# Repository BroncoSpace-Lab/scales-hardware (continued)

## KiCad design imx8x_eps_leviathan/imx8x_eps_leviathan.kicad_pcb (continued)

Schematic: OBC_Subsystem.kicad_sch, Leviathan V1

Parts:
C20: 220n; C0402; Voltage Rating +50v; LCSC C5159775
C21, C24, C28, C29, C30, C31: 100n; C0402; Voltage Rating +50v; LCSC C85858
C22: 22n; C0402; Voltage Rating +50v; LCSC C77023
C23: 0.47u; C0402; Voltage Rating +25V; LCSC C1623
C25: 10p; C0402; Voltage Rating +50v; LCSC C1545
C26, C27: 47u; CAP-SMD_L7.3-W4.3-FD; Voltage Rating +35v; LCSC C87110
L2: 6.1u; IND-SMD_FTKB1207-6R1NT; LCSC C3040409
R15: 1k; R0402; LCSC C54968
R16: 56.2k; R0402; LCSC C54968
R17: 10k; R0402; LCSC C25531
R18: 1k; R0402; LCSC C106235
R19: 15k; R0402; LCSC C114761
R21, R22, R23: 15k; R0402; LCSC C25756
R24: 14k; R_0603_1608Metric; LCSC C2930066
R25: 17k; R_0603_1608Metric; LCSC C137788
R26: 47k; R0402; LCSC C93943
R27: 2k; R0402; LCSC C60488
R28: 110k; R0402; LCSC C138065
R29, R30, R33, R34, R35, R36: 4.7k; R_0603_1608Metric; LCSC C99782
R31: 240k; R0402; LCSC C138029
R32: 100k; R0402; LCSC C60491
TP14, TP18, TP19, TP20, TP21, TP22: TestPoint; TestPoint_Pad_D1.0mm
U8: TPS1HB08BQPWPRQ1; HTSSOP-16_L5.0-W4.4-P0.65-LS6.4-TL-EP2.9; LCSC Part C3230075
U9: LTC6902; MSOP-10_L3.0-W3.0-P0.50-LS5.0-BL; LCSC C581012
U10: LT8612EUDE#PBF; QFN-28_L6.0-W3.0-P0.50-BL-EP; LCSC Part C580312
U11: TCA4307DGKR; VSSOP-8_L3.0-W3.0-P0.65-LS4.9-BL; LCSC Part C880333
U12: INA260AIPWR; TSSOP-16_L5.0-W4.4-P0.65-LS6.4-BL-1; LCSC Part C2155885

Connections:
+3.3V_OBC: C21.1, C30.1, C31.1, R24.1, R25.1, TP22.1, U9.1 (V+), U12.5 (A0), U12.10 (VS), U12.14 (IN-); also elsewhere on the board
+3.3V_OBC_Perif: C28.1, R29.1, R30.1, R33.1, R34.1, R35.1, R36.1, U11.8 (VCC); also elsewhere on the board
+V_Batt: C20.1, R16.2, TP14.1, U8.17 (VBB); also elsewhere on the board
GND: C20.2, C21.2, C22.2, C23.2, C26.2, C27.2, C28.2, C29.2, C30.2, C31.2, R17.1, R18.1, R19.1, R21.2, R22.2, R23.2, R27.2, R28.2, R32.2, U8.1 (GND), U9.8 (GND), U10.8 (PGND), U10.11 (GND), U10.25 (NC), U11.4 (GND), U12.4 (A1), U12.6 (GND); also elsewhere on the board
unnamed: R23.1, U8.15 (NC)
unnamed: R21.1, U8.16 (DIA_EN)
unnamed: R15.1, R16.1, R17.2, TP18.1, U8.4 (EN)
unnamed: R19.2, U8.3 (LATCH)
unnamed: R22.1, U8.14 (SEL1)
unnamed: R18.2, U8.2 (SNS)
unnamed: R24.2, U9.9 (MOD)
unnamed: R25.2, U9.10 (SET)
unnamed: C25.1, C26.1, C27.1, L2.2, R31.1, TP21.1, U10.22 (BIAS), U12.1 (IN+), U12.12 (VBUS)
unnamed: C24.1, U10.20 (BST)
unnamed: R26.2, R27.1, U10.4 (EN/UV)
unnamed: C25.2, R31.2, R32.1, U10.24 (FB)
unnamed: C29.1, U10.21 (INTVCC)
unnamed: R28.1, U10.3 (RT)
unnamed: C24.2, L2.1, U10.15 (SW)
unnamed: C23.1, U10.2 (TR/SS)
unnamed: C22.1, R26.1, TP19.1, U8.6 (VOUT), U10.5 (VIN)
unnamed: R33.2, U11.1 (EN)
unnamed: R34.2, U11.5 (READY)
SCL: R30.2, U11.3 (SCLIN), U12.9 (SCL); also elsewhere on the board
SDA: R29.2, U11.6 (SDAIN), U12.8 (SDA); also elsewhere on the board
SYNC_PHASE1: TP20.1, U9.4 (OUT1), U10.1 (SYNC)
SYNC_PHASE2: U9.5 (OUT2); also elsewhere on the board
SYNC_PHASE3: U9.6 (OUT3); also elsewhere on the board
X_ADMA_I2C0_SCL: R35.2, U11.2 (SCLOUT); also elsewhere on the board
X_ADMA_I2C0_SDA: R36.2, U11.7 (SDAOUT); also elsewhere on the board
~WD_EN_OBC: R15.2; also elsewhere on the board

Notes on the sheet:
Clock
OBC Subsystem
I2C Buffer
All Power related caps must +50v 0603/0402. Logic side can be 25V~16V 0402. Aim for getting them all to be ceramics, this is for flight readiness.
Clock is brought up with LT8612 OBC output. Set to 400Khz, SSFM on. 3 Phase setting
R63 and R64 set UVLO @ 24v.
Note: Symbol was modified so that pins were consolidated. This is chip is version B, so pin 5 is ILIM
LT8612 Config SYNC (Tied to Clock Phase 2) RT (Set default frequency to 400khz EN/UV threshold (~24v = UV, due to Li-ion discharge PGND (Tie to GND) DONE SW (Tie to inductor and setup the boost capacitor) BST (add 0.1uF bypass cap) INTVCC (add 0.1uF bypass cap) BIAS (If Vout is greater than 3.3v ti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
Vbatt = [24.0, 28.8, 33.6] Due to Li-ion battery charged and discharged states
L is calculated to 6.09u. Avoid Rounding.
SNS -> 1k -> GND : Not Using Latch -> 15k -> GND : Auto-retry Enabled SEL1 & SEL2 -> 15k -> GND : Diagnostics Disabled ILIM -> FLOAT -> Default Current Limit Set 42A
R65 and R66 set 3.3V Vout.
Vout -> 22nF Cap (Pg. 38)
C23 Changing to 0.47 for ~200ms startup time.
R16/R17 voltage divider to ensure at both high and low Lipo levels. OBC is always on. EN Pin pulled low by WD_EN_OBC on WD timeout
A0->Vs A1->GND I2C Address 1000001

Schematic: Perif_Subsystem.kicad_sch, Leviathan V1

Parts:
C32: 220n; C0402; Voltage Rating +50v; LCSC C5159775
C33: 22n; C0402; Voltage Rating +50v; LCSC C77023
C34: 0.47u; C0402; Voltage Rating +25V; LCSC C1623
C35, C39, C40, C41: 100n; C0402; Voltage Rating +50v; LCSC C85858
C36: 10p; C0402; Voltage Rating +50v; LCSC C1545
C37, C38: 47u; CAP-SMD_L7.3-W4.3-FD; Voltage Rating +35v; LCSC C87110
CN1: DF11-16DP-2DSA(08); CONN-TH_DF11-16DP-2DSA-08; LCSC Part C530981
L3: 10u; IND-SMD_L8.0-W8.0; LCSC C2849554
R37: 1k; R0402; LCSC C114761
R38: 1k; R0402; LCSC C106235
R39, R41, R42, R43: 15k; R0402; LCSC C114761
R44: 47k; R0402; LCSC C93943
R45: 2k; R0402; LCSC C60488
R46: 110k; R0402; LCSC C138065
R47: 20.8k; R0402; LCSC C25766
R48: 5k; R0402; LCSC C477765
TP23, TP24, TP31, TP32, TP33, TP34: TestPoint; TestPoint_Pad_D1.0mm
U13: TPS1HB08BQPWPRQ1; HTSSOP-16_L5.0-W4.4-P0.65-LS6.4-TL-EP2.9; LCSC Part C3230075
U14: LT8612EUDE#PBF; QFN-28_L6.0-W3.0-P0.50-BL-EP; LCSC Part C580312
U15: INA260AIPWR; TSSOP-16_L5.0-W4.4-P0.65-LS6.4-BL-1; LCSC Part C2155885

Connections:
+3.3V_OBC: C40.1, U15.4 (A1), U15.5 (A0), U15.10 (VS); also elsewhere on the board
+5V_Perif: C41.1, CN1.1, CN1.2, CN1.3, CN1.4, CN1.5, CN1.6, CN1.7, CN1.8, TP34.1, U15.14 (IN-)
+V_Batt: C32.1, TP24.1, U13.17 (VBB); also elsewhere on the board
GND: C32.2, C33.2, C34.2, C37.2, C38.2, C39.2, C40.2, C41.2, CN1.9, CN1.10, CN1.12, CN1.14, CN1.16, R38.1, R39.1, R41.1, R42.1, R43.1, R45.2, R46.2, R48.2, U13.1 (GND), U14.8 (PGND), U14.11 (GND), U14.25 (NC), U15.6 (GND); also elsewhere on the board
unnamed: R43.2, U13.15 (NC)
unnamed: R41.2, U13.16 (DIA_EN)
unnamed: R37.1, TP23.1, U13.4 (EN)
unnamed: R39.2, U13.3 (LATCH)
unnamed: R42.2, U13.14 (SEL1)
unnamed: R38.2, U13.2 (SNS)
unnamed: C33.1, R44.1, TP31.1, U13.6 (VOUT), U14.5 (VIN)
unnamed: C36.1, C37.1, C38.1, L3.2, R47.1, TP33.1, U14.22 (BIAS), U15.1 (IN+), U15.12 (VBUS)
unnamed: C35.1, U14.20 (BST)
unnamed: R44.2, R45.1, U14.4 (EN/UV)
unnamed: C36.2, R47.2, R48.1, U14.24 (FB)
unnamed: C39.1, U14.21 (INTVCC)
unnamed: R46.1, U14.3 (RT)
unnamed: C35.2, L3.1, U14.15 (SW)
unnamed: C34.1, U14.2 (TR/SS)
SCL: U15.9 (SCL); also elsewhere on the board
SDA: U15.8 (SDA); also elsewhere on the board
SYNC_PHASE2: TP32.1, U14.1 (SYNC); also elsewhere on the board
X_LSIO_GPIO1_IO18: R37.2; also elsewhere on the board

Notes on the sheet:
Peripheral Subsystem
Gecko Connector
L is calculated to 9.065. Avoid rounding.
Switch can be reset from the OBC by toggling the EN line, so no watchdog needed.
LT8612 Config SYNC (Tied to Clock Phase 2) RT (Set default frequency to 400khz EN/UV threshold (~24v = UV, due to Li-ion discharge PGND (Tie to GND) DONE SW (Tie to inductor and setup the boost capacitor) BST (add 0.1uF bypass cap) INTVCC (add 0.1uF bypass cap) BIAS (If Vout is greater than 3.3v ti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
Vout -> 22nF Cap (Pg. 38)
A0->Vs A1->VS I2C Address 1000101
C12 Changing to 0.47 for ~200ms startup time. I think this was the main issue for the brown outs. We werent meeting the startup time.
R83 and R101 set UVLO @ 24v
R103 and R104 set 5V Vout
All Power related caps must +50v 0603/0402. Logic side can be 25V~16V 0402.

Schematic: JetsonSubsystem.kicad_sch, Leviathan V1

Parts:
C10: 220n; C0402; Voltage Rating +50v; LCSC C5159775
C11: 22n; C0402; Voltage Rating +50v; LCSC C77023
C12: 1u; C0402; Voltage Rating +10V; LCSC C14445
C13, C17, C18, C19: 100n; C0402; Voltage Rating +50v; LCSC C85858
C14: 10p; C0402; Voltage Rating +50v; LCSC C1545
C15, C16: 47u; CAP-SMD_L7.3-W4.3-FD; Voltage Rating +35v; LCSC C87110
J5: DF11-16DP-2DSA; CONN-TH_DF11-16DP-2DSA-08; LCSC Part C530981
L1: 35u; IND-SMD_L10.7-W10.0_ETQP5MXXXX; LCSC C2880058
R1, R2: 1k; R0402; LCSC C114761
R3, R5, R7, R8, R9: 15k; R0402; LCSC C114761
R4: 1k; R0402; LCSC C106235
R10: 47k; R0402; LCSC C93943
R11: 2k; R0402; LCSC C60488
R12: 110k; R0402; LCSC C138065
R13: 196k; R0402; LCSC C2077051
R14: 10k; R0402; LCSC C25531
TP1, TP2, TP10, TP11, TP12, TP13: TestPoint; TestPoint_Pad_D1.0mm
U5: TPS1HB08BQPWPRQ1; HTSSOP-16_L5.0-W4.4-P0.65-LS6.4-TL-EP2.9; LCSC Part C3230075
U6: LT8612EUDE#PBF; QFN-28_L6.0-W3.0-P0.50-BL-EP; LCSC Part C580312
U7: INA260AIPWR; TSSOP-16_L5.0-W4.4-P0.65-LS6.4-BL-1; LCSC Part C2155885

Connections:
+3.3V_OBC: C18.1, U7.10 (VS); also elsewhere on the board
+20V_Jetson: C19.1, J5.1, J5.2, J5.3, J5.4, J5.5, J5.6, J5.7, J5.8, TP13.1, U7.14 (IN-); also elsewhere on the board
+V_Batt: C10.1, TP2.1, U5.17 (VBB); also elsewhere on the board
GND: C10.2, C11.2, C12.2, C15.2, C16.2, C17.2, C18.2, C19.2, J5.9, J5.10, J5.11, J5.12, J5.13, J5.15, R3.2, R4.1, R5.2, R7.2, R8.2, R9.2, R11.2, R12.2, R14.2, U5.1 (GND), U6.8 (PGND), U6.11 (GND), U6.25 (NC), U7.4 (A1), U7.5 (A0), U7.6 (GND); also elsewhere on the board
unnamed: J5.14, J5.16
unnamed: R9.1, U5.15 (NC)
unnamed: R7.1, U5.16 (DIA_EN)
unnamed: R1.2, R2.1, R3.1, TP1.1, U5.4 (EN)
unnamed: R5.1, U5.3 (LATCH)
unnamed: R8.1, U5.14 (SEL1)
unnamed: R4.2, U5.2 (SNS)
unnamed: C11.1, R10.1, TP10.1, U5.6 (VOUT), U6.5 (VIN)
unnamed: C14.1, C15.1, C16.1, L1.2, R13.1, TP12.1, U6.22 (BIAS), U7.1 (IN+), U7.12 (VBUS)
unnamed: C13.1, U6.20 (BST)
unnamed: R10.2, R11.1, U6.4 (EN/UV)
unnamed: C14.2, R13.2, R14.1, U6.24 (FB)
unnamed: C17.1, U6.21 (INTVCC)
unnamed: R12.1, U6.3 (RT)
unnamed: C13.2, L1.1, U6.15 (SW)
unnamed: C12.1, U6.2 (TR/SS)
SCL: U7.9 (SCL); also elsewhere on the board
SDA: U7.8 (SDA); also elsewhere on the board
SYNC_PHASE3: TP11.1, U6.1 (SYNC); also elsewhere on the board
X_LSIO_GPIO1_IO19: R1.1; also elsewhere on the board
~WD_EN_JETSON: R2.2; also elsewhere on the board

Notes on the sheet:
Jetson Power Subsystem
Gecko Connector
All Power related caps must +50v 0603/0402. Logic side can be 25V~16V 0402.
R3 is a pull down to bias the EN pin OFF, WD_EN_JETSON and GPIO float unless asserted. OBC_EN is 3.3v. On High, 3.3*(15k/1k+15k) = 3.09v > 2V for EN
To configure: (Pg.8) SYNC (Tied to Clock Phase 2) RT (Set default frequency to 400khz EN/UV threshold (~24v = UV, due to Li-ion discharge PGND (Tie to GND) DONE SW (Tie to inductor and setup the boost capacitor) BST (add 0.1uF bypass cap) INTVCC (add 0.1uF bypass cap) BIAS (If Vout is greater than 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
L is calculated to be 35.315uH. Avoid rounding.
Vout -> 22nF Cap (Pg. 38)
C12 = to 1u for ~500ms startup time. Validated in LTSPICE
EN Pin Pulled up by GPIO on IMX8X to enable subsystem. WD_EN_JETSON is pulled low on WD timeout. 42s
R10 and R11 set UVLO @ 24v
A0->GND A1->GND I2C Address 1000000
R13 and R14 set 20V Vout

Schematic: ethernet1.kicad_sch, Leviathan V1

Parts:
R163: 200; R0402
R164: 22; R0402
R165: 10K; R0402
R166: 2.49K; R0402
RJ2: RJHSE5384; RJ45-TH_RJHSE5384; LCSC Part C464587
TV4, TV5: SRV05-4.TCT; SOT-23-6_L2.9-W1.6-P0.95-LS2.8-BR; LCSC Part C13612

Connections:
+3.3V_OBC_Perif: R165.2, R166.1, RJ2.10 (L+), RJ2.12 (R+); also elsewhere on the board
ETH1_A_TX_N: RJ2.2, TV4.1; also elsewhere on the board
ETH1_A_TX_P: RJ2.1, TV4.3; also elsewhere on the board
ETH1_B_TX_N: RJ2.6, TV4.6; also elsewhere on the board
ETH1_B_TX_P: RJ2.3, TV4.4, TV5.1; also elsewhere on the board
ETH1_C_TXCLK_N: RJ2.5; also elsewhere on the board
ETH1_C_TXCLK_P: RJ2.4, TV5.3; also elsewhere on the board
ETH1_D_RXDV_N: RJ2.8, TV5.4; also elsewhere on the board
ETH1_D_RXDV_P: RJ2.7, TV5.6; also elsewhere on the board
ETH1_LED0: R164.2, R166.2; also elsewhere on the board
ETH1_LED2: R163.1, R165.1; also elsewhere on the board
GND: TV4.2, TV5.2; also elsewhere on the board
GNDPWR: RJ2.13 (SHELL), RJ2.14 (SHELL); also elsewhere on the board
unnamed: R164.1, RJ2.9 (L-)
unnamed: R163.2, RJ2.11 (R-)

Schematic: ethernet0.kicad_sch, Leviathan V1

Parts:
R159: 200; R0402
R160: 22; R0402
R161: 10K; R0402
R162: 2.49K; R0402
RJ1: RJHSE5384; RJ45-TH_RJHSE5384; LCSC Part C464587
TV2, TV3: SRV05-4.TCT; SOT-23-6_L2.9-W1.6-P0.95-LS2.8-BR; LCSC Part C13612

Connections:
+3.3V_OBC_Perif: R161.2, R162.1, RJ1.10 (L+), RJ1.12 (R+); also elsewhere on the board
GND: TV2.2, TV3.2; also elsewhere on the board
GNDPWR: RJ1.13 (SHELL), RJ1.14 (SHELL); also elsewhere on the board
unnamed: R160.1, RJ1.9 (L-)
unnamed: R159.2, RJ1.11 (R-)
X_ETH0_A_TX_N: RJ1.2, TV2.1; also elsewhere on the board
X_ETH0_A_TX_P: RJ1.1, TV2.3; also elsewhere on the board
X_ETH0_B_TX_N: RJ1.6, TV2.6; also elsewhere on the board
X_ETH0_B_TX_P: RJ1.3, TV2.4, TV3.1; also elsewhere on the board
X_ETH0_C_TXCLK_N: RJ1.5; also elsewhere on the board
X_ETH0_C_TXCLK_P: RJ1.4, TV3.3; also elsewhere on the board
X_ETH0_D_RXDV_N: RJ1.8, TV3.4; also elsewhere on the board
X_ETH0_D_RXDV_P: RJ1.7, TV3.6; also elsewhere on the board
X_ETH0_LED0: R160.2, R162.2; also elsewhere on the board
X_ETH0_LED1: R159.1, R161.1; also elsewhere on the board

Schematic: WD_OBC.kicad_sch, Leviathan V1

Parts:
C42, C43, C44: 100uF; CAP-SMD_L7.3-W6.1_TCN4227M025R0100; LCSC Part C2158793
C45, C46, C47, C48, C49: 10u; C0402; LCSC 194427
D4, D6: 1N4448WS-7-F; SOD-323_L1.8-W1.3-LS2.5-RD; MPN 1N4151WS-E3-08; LCSC C2979762
D5: GREEN; LED_0603_1608Metric; MPN 150060GS75000; LCSC C965799
JP1: SolderJumper_2_Open; SolderJumper-2_P1.3mm_Open_RoundedPad1.0x1.5mm
R49: 10; R_1206_3216Metric; MPN ESR18EZPF10R0; LCSC C17903
R50, R51, R52, R53, R56, R57: 10k; R0402; LCSC C25531
R54, R55: 3k; R0402; LCSC C2909355
R58, R60: 1k; R0402; LCSC C106235
R59, R61, R62, R64, R65: 100k; R0402; LCSC C269673
R63: 4.7M; R0402; LCSC C474132
TP36: TestPoint; TestPoint_Pad_D1.0mm
U16: TLV1704; TSSOP-14_4.4x5mm_P0.65mm; MPN TLV1704AQPWRQ1; LCSC C181596

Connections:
+3.3V_OBC: D4.2 (A); also elsewhere on the board
/SCALES_EPS/OBC_Subsystem/WD_OBC/WDT-VIN: C42.1, C43.1, C44.1, R49.2, R50.2, R59.1, R65.1, U16.3 (V+)
/SCALES_EPS/OBC_Subsystem/WD_OBC/WDT-VP: R53.1, R54.2, U16.5 (+)
GND: C42.2, C43.2, C44.2, C46.1, C47.1, C48.1, C49.1, D5.1 (K), R54.1, R56.1, U16.12 (V-); also elsewhere on the board
unnamed: C45.2, R56.2, R57.2
unnamed: D4.1 (C), R49.1
unnamed: D5.2 (A), R55.1
unnamed: D6.2 (A), R62.2
unnamed: D6.1 (C), R63.2, R64.2, R65.2, U16.11 (+), U16.14
unnamed: JP1.1 (A), U16.13
unnamed: R50.1, R51.2, R61.1
unnamed: R58.2, U16.2
unnamed: R60.2, U16.1
unnamed: R57.1, U16.4 (-)
unnamed: C46.2, R58.1, R59.2, U16.7 (+)
unnamed: R52.1, R53.2, U16.6 (-)
unnamed: R61.2, R64.1, U16.9 (+)
unnamed: C47.2, C48.2, R60.1, R62.1, R63.1, U16.8 (-)
unnamed: C49.2, R51.1, R52.2, U16.10 (-)
X_LSIO_GPIO1_IO20: C45.1, R55.2, TP36.1; also elsewhere on the board
~WD_EN_OBC: JP1.2 (B); also elsewhere on the board

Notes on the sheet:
Select 15V-25V on C21, C22, C23
C112+C114 and R62+R63 set the WDT frequency
WDT enabled when soldered
Oscillator
TLV1704AMPWPSEP is the radiation tolerant version. Use TLV1704AQPWRQ1 for non-flight C3 boards.
External Watch-Dog Timer
DC block and pulse detector
~ 24 s period (36 s on power up)
D5 and D7 MUST be 1N4151WS
Disable shutdown during initial power up.
Pulse integrator
Output buffer
Not using the recommended diode due to lack of stock. The DIP is almost exactly the same.
300uF Capacitance used to keep WD output high after reset for 1s to allow for subsystem power cycle
WD_EN_Perif goes to EN of the load switch controller

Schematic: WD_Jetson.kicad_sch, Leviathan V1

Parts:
C50, C51, C52: 100uF; CAP-SMD_L7.3-W6.1_TCN4227M025R0100; LCSC Part C2158793
C53, C56, C57: 10u; C0402; LCSC 194427
C54, C55: 10u; C0402
D7, D9: 1N4448WS-7-F; SOD-323_L1.8-W1.3-LS2.5-RD; MPN 1N4151WS-E3-08; LCSC C2979762
D8: GREEN; LED_0603_1608Metric; MPN 150060GS75000; LCSC C965799
JP2: SolderJumper_2_Open; SolderJumper-2_P1.3mm_Open_RoundedPad1.0x1.5mm
R66: 10; R_1206_3216Metric; MPN ESR18EZPF10R0; LCSC C17903
R67, R77, R79, R80, R82, R83: 100k; R0402; LCSC C269673
R68, R69, R70, R71, R74, R75: 10k; R0402; LCSC C25531
R72, R73: 3k; R0402; LCSC C2909355
R76, R78: 1k; R0402; LCSC C106235
R81: 4.7M; R0402; LCSC C474132
TP42: TestPoint; TestPoint_Pad_D1.0mm
U17: TLV1704; TSSOP-14_4.4x5mm_P0.65mm; MPN TLV1704AQPWRQ1; LCSC C181596

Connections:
+20V_Jetson: D7.2 (A); also elsewhere on the board
/SCALES_EPS/Jetson_Subsystem/WD_Jetson/WDT-VIN: R67.2, R68.2, R77.1, R83.1
/SCALES_EPS/Jetson_Subsystem/WD_Jetson/WDT-VP: R71.1, R72.2, U17.5 (+)
GND: C50.2, C51.2, C52.2, C54.1, C55.1, C56.1, C57.1, D8.1 (K), R72.1, R74.1, U17.12 (V-); also elsewhere on the board
unnamed: C53.2, R74.2, R75.2
unnamed: D7.1 (C), R66.1
unnamed: D8.2 (A), R73.1
unnamed: D9.2 (A), R80.2
unnamed: D9.1 (C), R81.2, R82.2, R83.2, U17.11 (+), U17.14
unnamed: JP2.1 (A), U17.13
unnamed: R68.1, R69.2, R79.1
unnamed: R76.2, U17.2
unnamed: R78.2, U17.1
unnamed: R75.1, U17.4 (-)
unnamed: C54.2, R76.1, R77.2, U17.7 (+)
unnamed: R70.1, R71.2, U17.6 (-)
unnamed: R79.2, R82.1, U17.9 (+)
unnamed: C55.2, C56.2, R78.1, R80.1, R81.1, U17.8 (-)
unnamed: C57.2, R69.1, R70.2, U17.10 (-)
unnamed: C50.1, C51.1, C52.1, R66.2, R67.1, U17.3 (V+)
X_LSIO_GPIO1_IO19: C53.1, R73.2, TP42.1; also elsewhere on the board
~WD_EN_JETSON: JP2.2 (B); also elsewhere on the board

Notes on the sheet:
Pulse integrator
TLV1704AMPWPSEP is the radiation tolerant version. Use TLV1704AQPWRQ1 for non-flight C3 boards.
Oscillator
Select 15V-25V on C21, C22, C23
WDT enabled when soldered
C112+C114 and R62+R63 set the WDT frequency
Disable shutdown during initial power up.
~ 24 s period (36 s on power up)
External Watch-Dog Timer
DC block and pulse detector
D5 and D7 MUST be 1N4151WS
Output buffer
Caps must be 0402 10v 10uf
Adding a little voltage divider here so that the 10uf 10v caps dont explode.
300uF Capacitance used to keep WD output high after reset for 1s to allow for subsystem power cycle

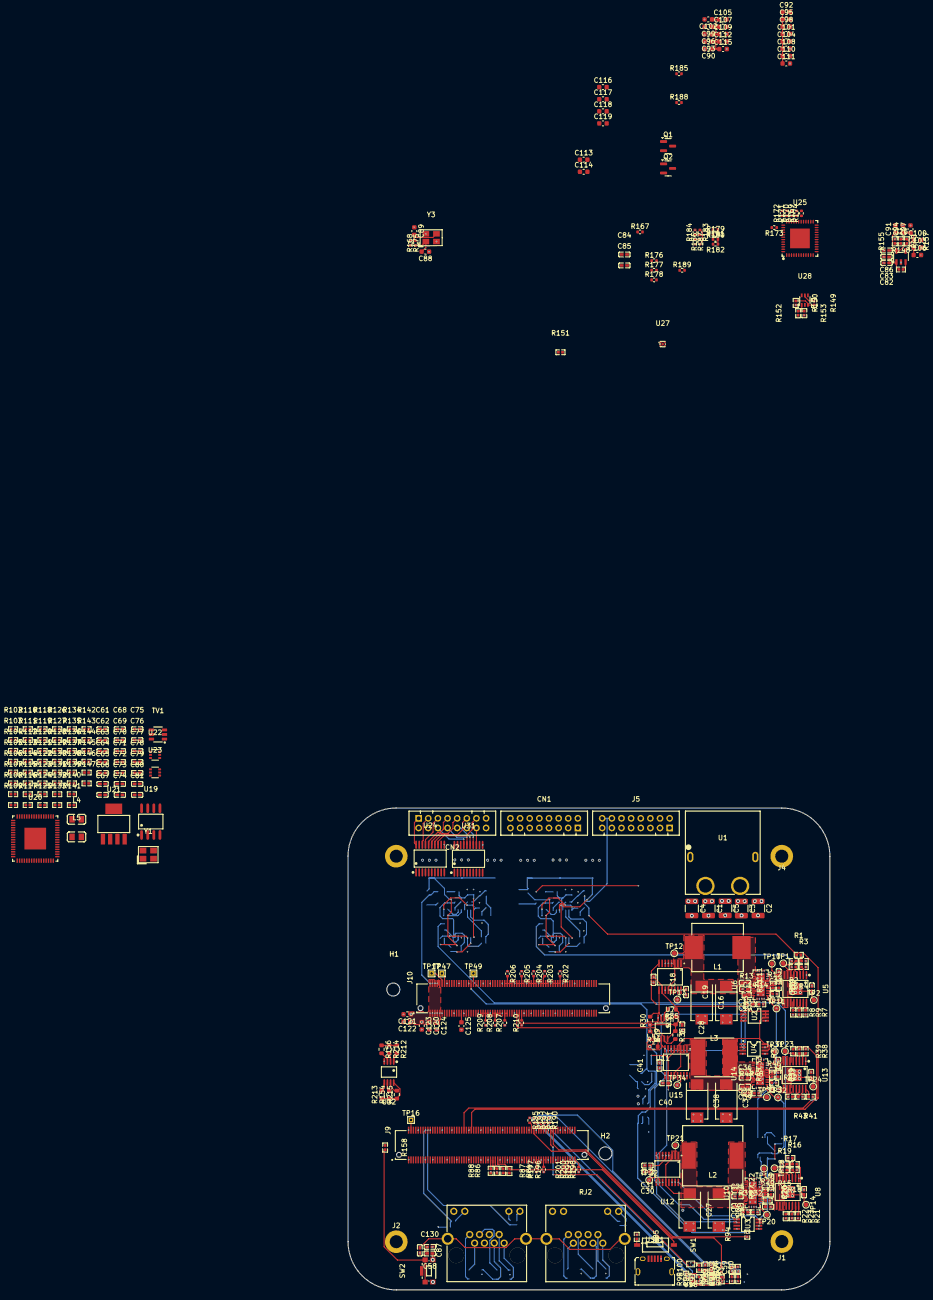
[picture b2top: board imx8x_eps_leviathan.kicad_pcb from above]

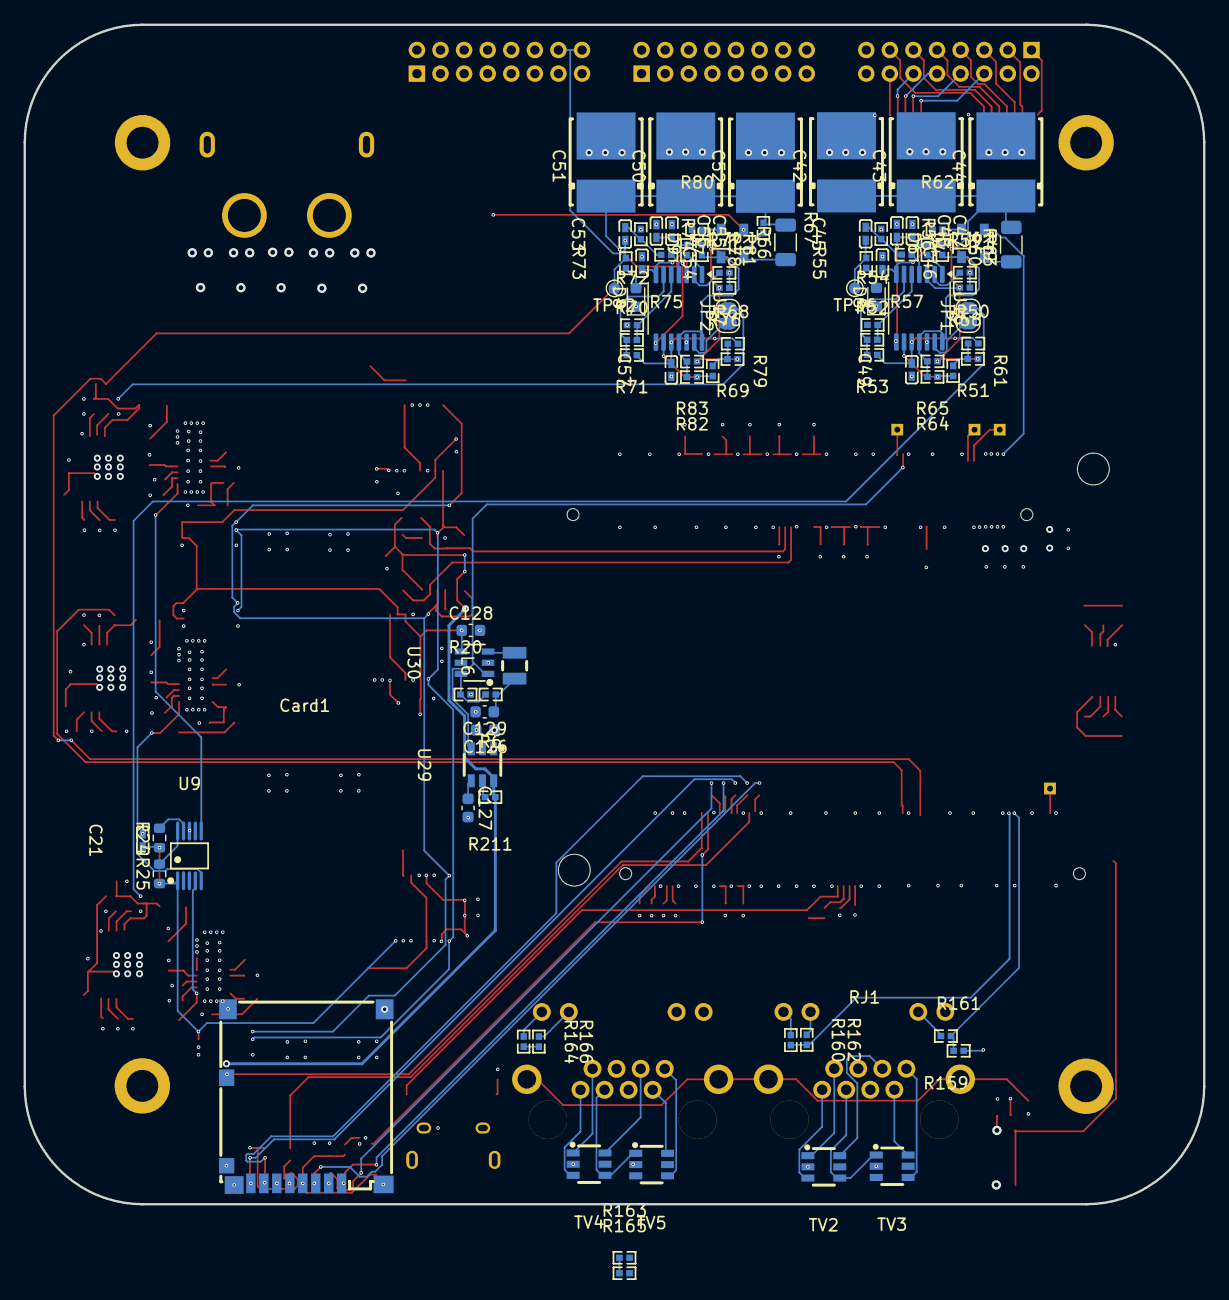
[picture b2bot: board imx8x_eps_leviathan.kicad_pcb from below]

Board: 6 copper layers, 100.0 x 100.0 mm, 436 parts (90 on the bottom side), 313 nets.

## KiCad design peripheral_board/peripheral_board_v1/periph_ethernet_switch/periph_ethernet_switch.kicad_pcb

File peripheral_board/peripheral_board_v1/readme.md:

# This is the second revision of the peripheral board.
    This board went from having a raspberry pi pico2 to having just an Etherent switch. The reason being is that this addition of low level sensors can be used on the flight control computer. This eliminates another system archetecture and give the end user the ability to create their own custom peripheral baord that can be added to a local area network.

    This makes this board just an Ethernet switch daughter board that is full optional.

## Changes from v0 to V1
    Moved away from the microcontroller to just being the multi-port ethernet switch.

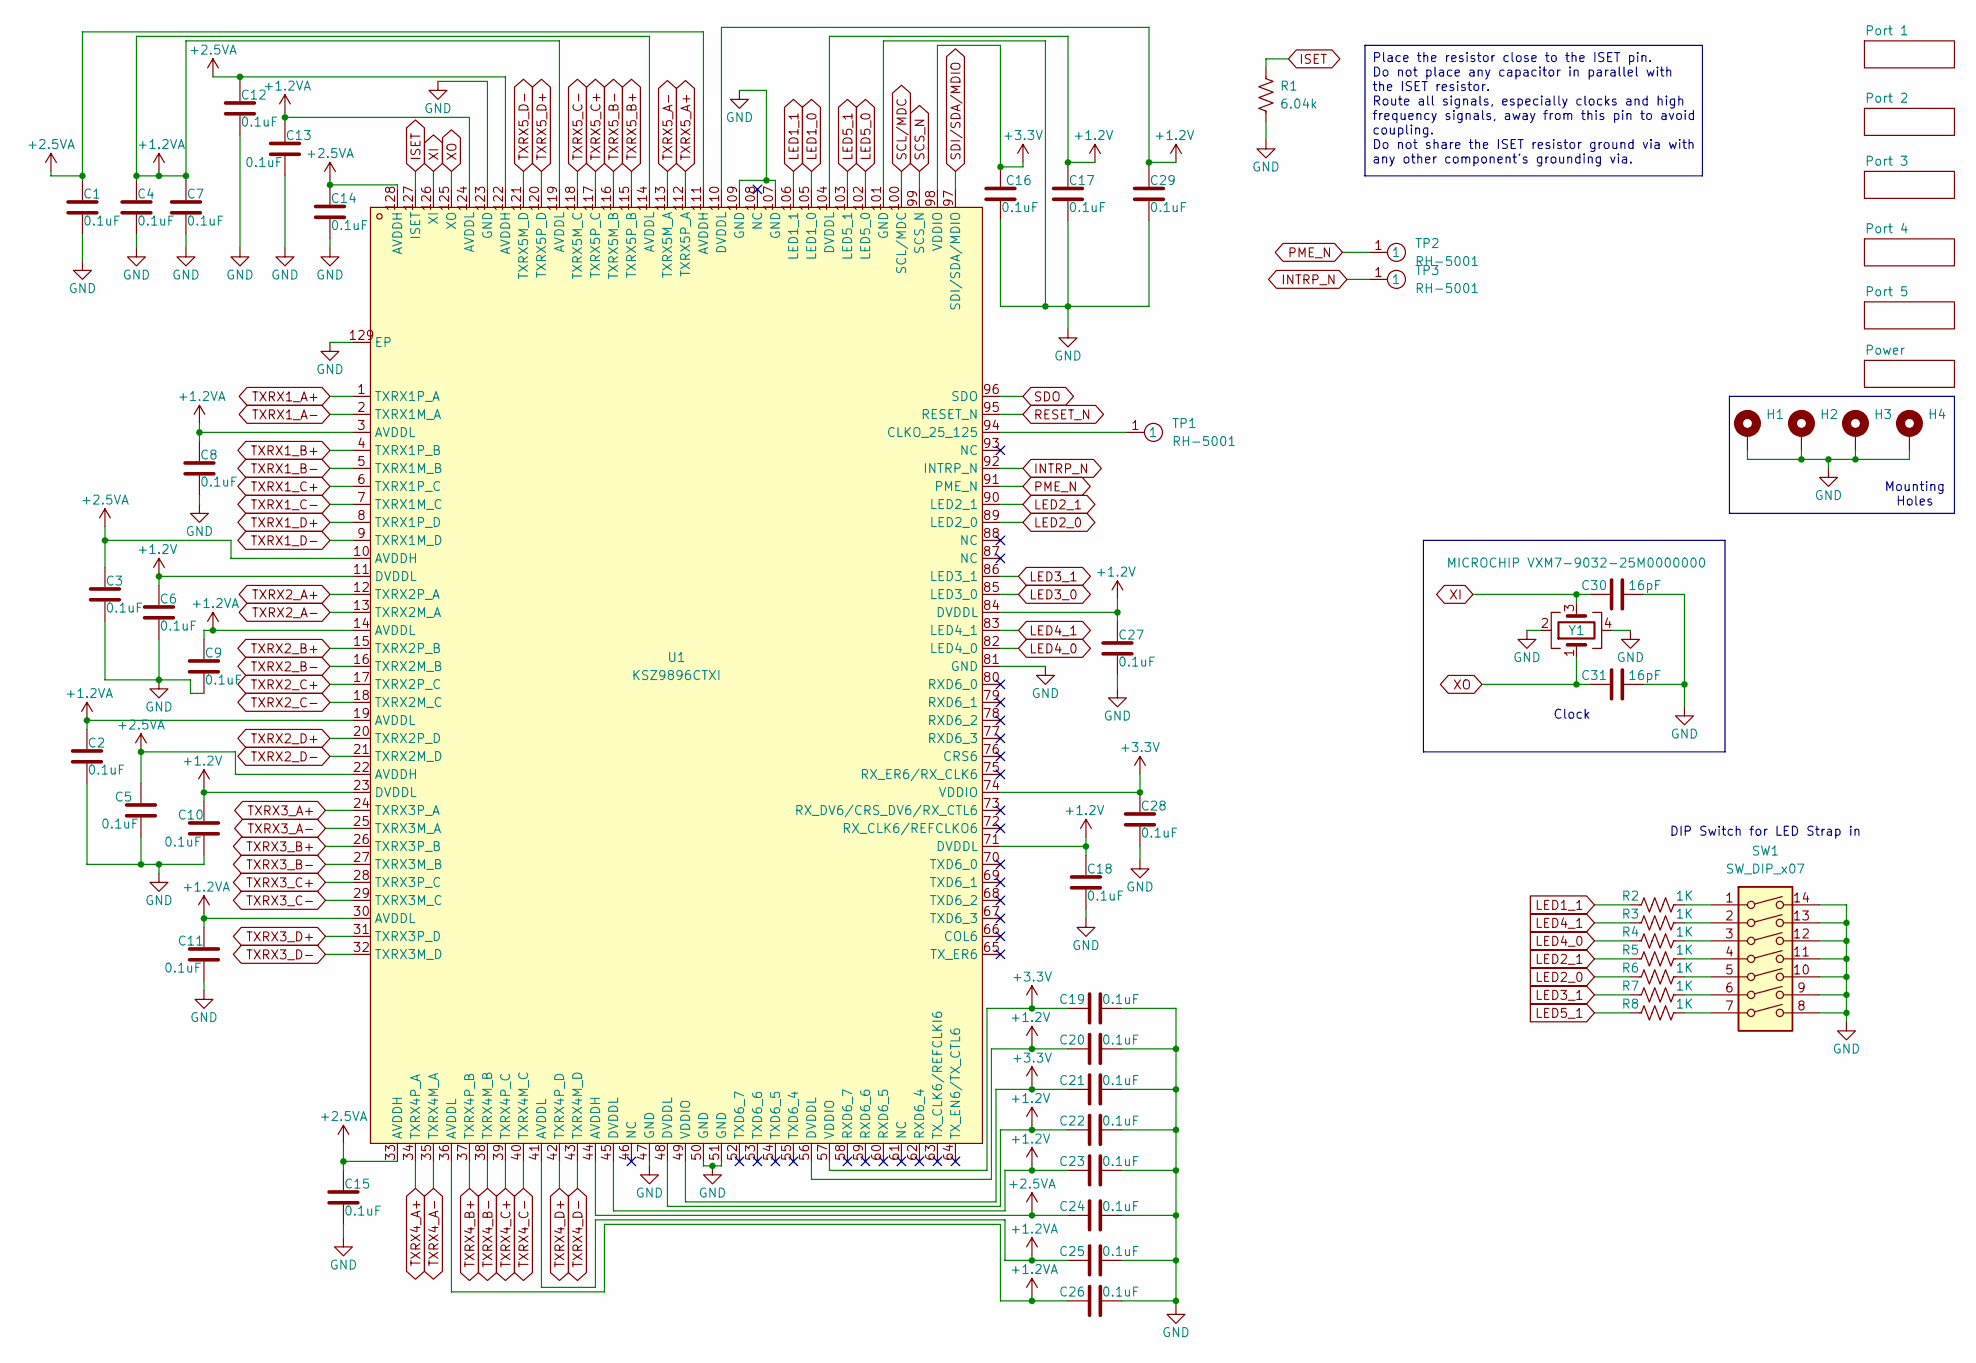
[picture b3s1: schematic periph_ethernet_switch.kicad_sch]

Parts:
C1, C2, C3, C4, C5, C6, C7, C8, C9, C10, C11, C12, C13, C14, C15, C16, C17, C18, C19, C20, C21, C22, C23, C24, C25, C26, C27, C28, C29: 0.1uF; C_0603_1608Metric
C30, C31: 16pF; C_0603_1608Metric
H1, H2, H3, H4: MountingHole; MountingHole_3mm_Pad
R1: 6.04k; R_0603_1608Metric
R2, R3, R4, R5, R6, R7, R8: 1K; R_0603_1608Metric
SW1: SW_DIP_x07; SW_DIP_SPSTx07_Slide_6.7x19.34mm_W7.62mm_P2.54mm_LowProfile
TP1, TP2, TP3: RH-5001; TEST-TH_BD2.54-P1.4_BLACK; LCSC Part C5199801
U1: KSZ9896CTXI; TQFP-128_L14.0-W14.0-P0.40-LS16.0-BL-EP; LCSC Part C638297
Y1: MICROCHIP VXM7-9032-25M0000000; CRYSTAL-SMD_4P-L3.2-W2.5-BL

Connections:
+1.2V: C6.1, C10.1, C17.1, C18.1, C20.1, C22.1, C23.1, C27.1, C29.1, U1.11 (DVDDL), U1.23 (DVDDL), U1.45 (DVDDL), U1.48 (DVDDL), U1.56 (DVDDL), U1.71 (DVDDL), U1.84 (DVDDL), U1.104 (DVDDL), U1.110 (DVDDL); also elsewhere on the board
+1.2VA: C2.1, C4.1, C7.1, C8.1, C9.1, C11.1, C13.1, C25.1, C26.1, U1.3 (AVDDL), U1.14 (AVDDL), U1.19 (AVDDL), U1.30 (AVDDL), U1.36 (AVDDL), U1.41 (AVDDL), U1.114 (AVDDL), U1.119 (AVDDL), U1.124 (AVDDL); also elsewhere on the board
+2.5VA: C1.1, C3.1, C5.1, C12.1, C14.1, C15.1, C24.1, U1.10 (AVDDH), U1.22 (AVDDH), U1.33 (AVDDH), U1.44 (AVDDH), U1.111 (AVDDH), U1.122 (AVDDH), U1.128 (AVDDH); also elsewhere on the board
INTRP_N: TP3.1, U1.92 (INTRP_N)
ISET: R1.2, U1.127 (ISET)
LED1_0: U1.105 (LED1_0); also elsewhere on the board
LED1_1: R2.2, U1.106 (LED1_1); also elsewhere on the board
LED2_0: R6.2, U1.89 (LED2_0); also elsewhere on the board
LED2_1: R5.2, U1.90 (LED2_1); also elsewhere on the board
LED3_0: U1.85 (LED3_0); also elsewhere on the board
LED3_1: R7.2, U1.86 (LED3_1); also elsewhere on the board
LED4_0: R4.2, U1.82 (LED4_0); also elsewhere on the board
LED4_1: R3.2, U1.83 (LED4_1); also elsewhere on the board
LED5_0: U1.102 (LED5_0); also elsewhere on the board
LED5_1: R8.2, U1.103 (LED5_1); also elsewhere on the board
unnamed: R2.1, SW1.1
unnamed: R3.1, SW1.2
unnamed: R4.1, SW1.3
unnamed: R5.1, SW1.4
unnamed: R6.1, SW1.5
unnamed: R7.1, SW1.6
unnamed: R8.1, SW1.7
unnamed: TP1.1, U1.94 (CLKO_25_125)
PME_N: TP2.1, U1.91 (PME_N)
RESET_N: U1.95 (RESET_N); also elsewhere on the board
SCL/MDC: U1.100 (SCL/MDC); also elsewhere on the board
SCS_N: U1.99 (SCS_N); also elsewhere on the board
SDI/SDA/MDIO: U1.97 (SDI/SDA/MDIO); also elsewhere on the board
SDO: U1.96 (SDO); also elsewhere on the board
TXRX1_A+: U1.1 (TXRX1P_A); also elsewhere on the board
TXRX1_A-: U1.2 (TXRX1M_A); also elsewhere on the board
TXRX1_B+: U1.4 (TXRX1P_B); also elsewhere on the board
TXRX1_B-: U1.5 (TXRX1M_B); also elsewhere on the board
TXRX1_C+: U1.6 (TXRX1P_C); also elsewhere on the board
TXRX1_C-: U1.7 (TXRX1M_C); also elsewhere on the board
TXRX1_D+: U1.8 (TXRX1P_D); also elsewhere on the board
TXRX1_D-: U1.9 (TXRX1M_D); also elsewhere on the board
TXRX2_A+: U1.12 (TXRX2P_A); also elsewhere on the board
TXRX2_A-: U1.13 (TXRX2M_A); also elsewhere on the board
TXRX2_B+: U1.15 (TXRX2P_B); also elsewhere on the board
TXRX2_B-: U1.16 (TXRX2M_B); also elsewhere on the board
TXRX2_C+: U1.17 (TXRX2P_C); also elsewhere on the board
TXRX2_C-: U1.18 (TXRX2M_C); also elsewhere on the board
TXRX2_D+: U1.20 (TXRX2P_D); also elsewhere on the board
TXRX2_D-: U1.21 (TXRX2M_D); also elsewhere on the board
TXRX3_A+: U1.24 (TXRX3P_A); also elsewhere on the board
TXRX3_A-: U1.25 (TXRX3M_A); also elsewhere on the board
TXRX3_B+: U1.26 (TXRX3P_B); also elsewhere on the board
TXRX3_B-: U1.27 (TXRX3M_B); also elsewhere on the board
TXRX3_C+: U1.28 (TXRX3P_C); also elsewhere on the board
TXRX3_C-: U1.29 (TXRX3M_C); also elsewhere on the board
TXRX3_D+: U1.31 (TXRX3P_D); also elsewhere on the board
TXRX3_D-: U1.32 (TXRX3M_D); also elsewhere on the board
TXRX4_A+: U1.34 (TXRX4P_A); also elsewhere on the board
TXRX4_A-: U1.35 (TXRX4M_A); also elsewhere on the board
TXRX4_B+: U1.37 (TXRX4P_B); also elsewhere on the board
TXRX4_B-: U1.38 (TXRX4M_B); also elsewhere on the board
TXRX4_C+: U1.39 (TXRX4P_C); also elsewhere on the board
TXRX4_C-: U1.40 (TXRX4M_C); also elsewhere on the board
TXRX4_D+: U1.42 (TXRX4P_D); also elsewhere on the board
TXRX4_D-: U1.43 (TXRX4M_D); also elsewhere on the board
TXRX5_A+: U1.112 (TXRX5P_A); also elsewhere on the board
TXRX5_A-: U1.113 (TXRX5M_A); also elsewhere on the board
TXRX5_B+: U1.115 (TXRX5P_B); also elsewhere on the board
TXRX5_B-: U1.116 (TXRX5M_B); also elsewhere on the board
TXRX5_C+: U1.117 (TXRX5P_C); also elsewhere on the board
TXRX5_C-: U1.118 (TXRX5M_C); also elsewhere on the board
TXRX5_D+: U1.120 (TXRX5P_D); also elsewhere on the board
TXRX5_D-: U1.121 (TXRX5M_D); also elsewhere on the board
XI: C30.1, U1.126 (XI), Y1.3
XO: C31.1, U1.125 (XO), Y1.1

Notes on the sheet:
Mounting Holes
DIP Switch for LED Strap in
Clock
Place the resistor close to the ISET pin. Do not place any capacitor in parallel with the ISET resistor. Route all signals, especially clocks and high frequency signals, away from this pin to avoid coupling. Do not share the ISET resistor ground via with any other component's grounding via.

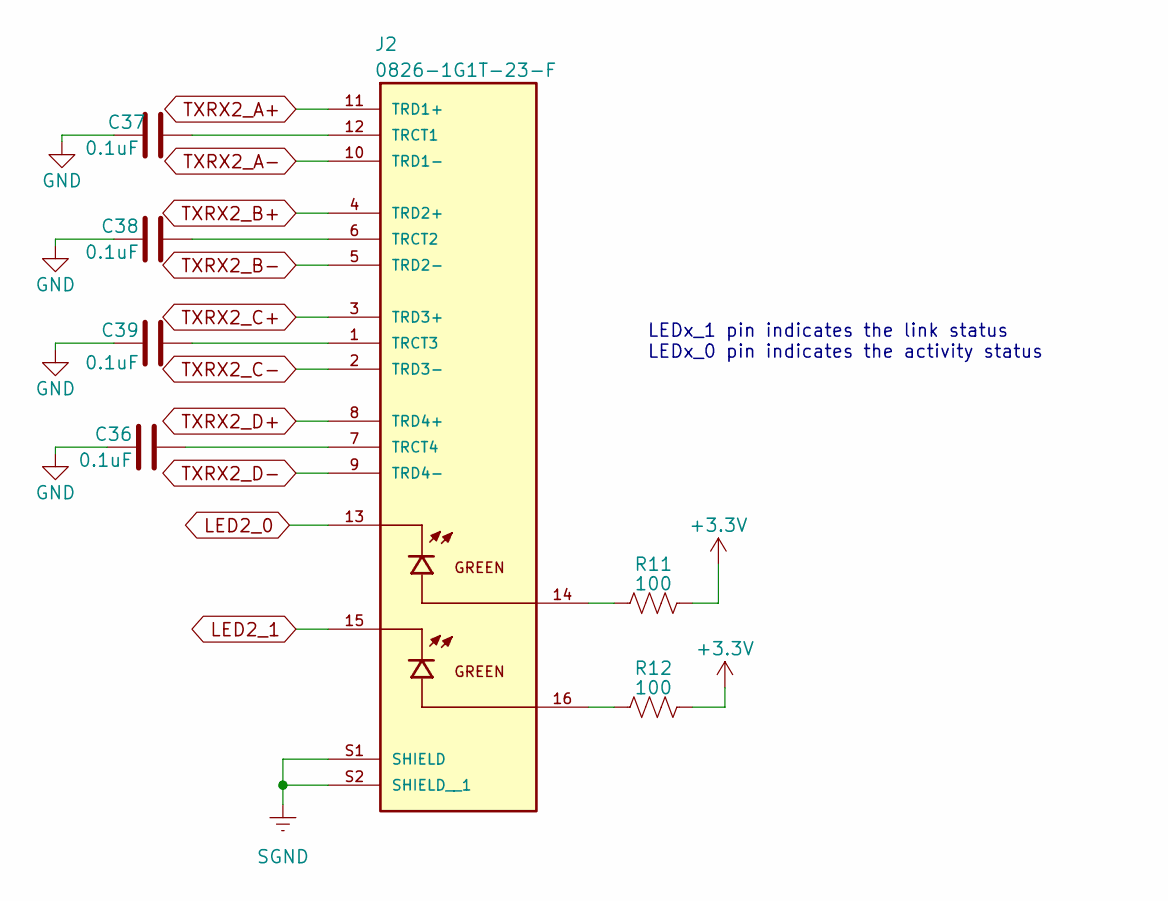
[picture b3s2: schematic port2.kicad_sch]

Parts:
C36, C37, C38, C39: 0.1uF; C_0603_1608Metric
J2: 0826-1G1T-23-F; BEL_0826-1G1T-23-F
R11, R12: 100; R_0603_1608Metric

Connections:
LED2_0: J2.13; also elsewhere on the board
LED2_1: J2.15; also elsewhere on the board
unnamed: J2.14, R11.2
unnamed: J2.16, R12.2
unnamed: C37.2, J2.12 (TRCT1)
unnamed: C38.2, J2.6 (TRCT2)
unnamed: C39.2, J2.1 (TRCT3)
unnamed: C36.2, J2.7 (TRCT4)
SGND: J2.S1 (SHIELD), J2.S2 (SHIELD__1); also elsewhere on the board
TXRX2_A+: J2.11 (TRD1+); also elsewhere on the board
TXRX2_A-: J2.10 (TRD1-); also elsewhere on the board
TXRX2_B+: J2.4 (TRD2+); also elsewhere on the board
TXRX2_B-: J2.5 (TRD2-); also elsewhere on the board
TXRX2_C+: J2.3 (TRD3+); also elsewhere on the board
TXRX2_C-: J2.2 (TRD3-); also elsewhere on the board
TXRX2_D+: J2.8 (TRD4+); also elsewhere on the board
TXRX2_D-: J2.9 (TRD4-); also elsewhere on the board

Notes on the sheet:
LEDx_1 pin indicates the link status LEDx_0 pin indicates the activity status

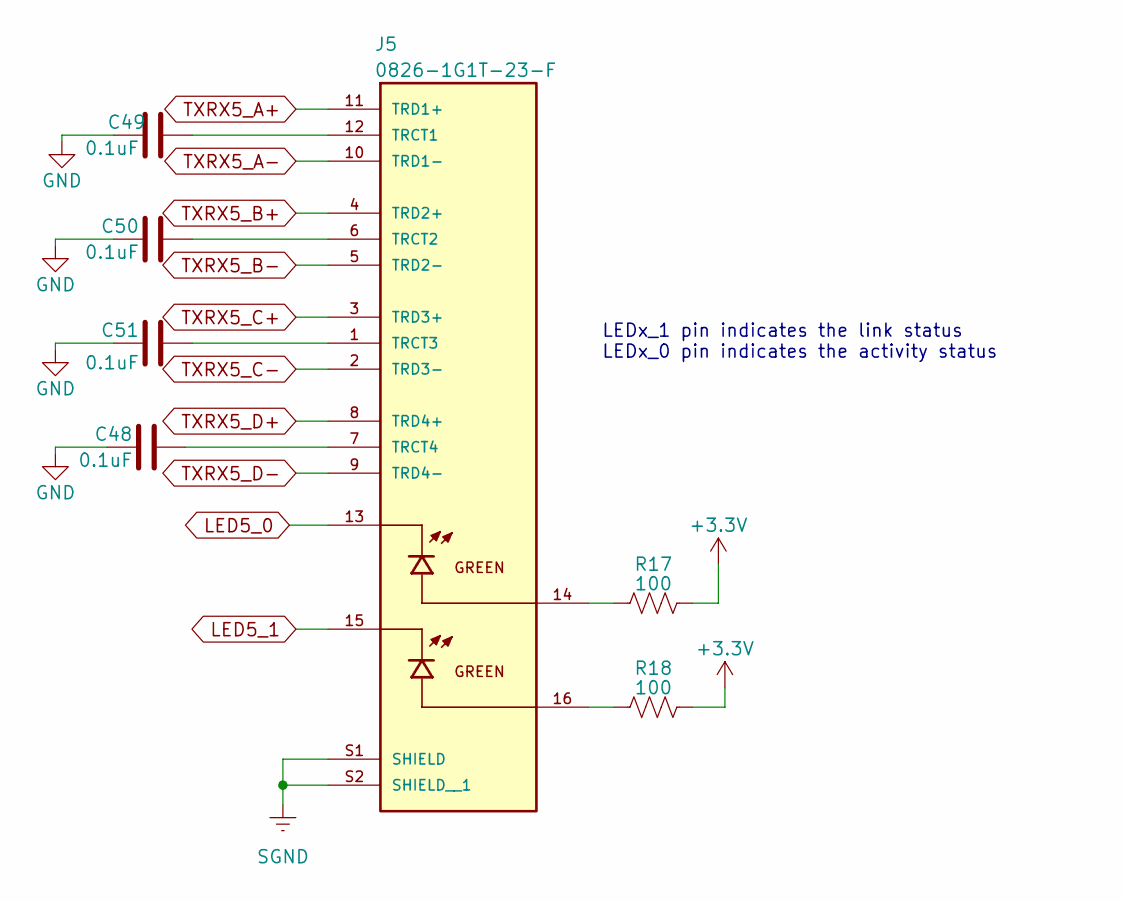
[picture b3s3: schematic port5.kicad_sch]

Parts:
C48, C49, C50, C51: 0.1uF; C_0603_1608Metric
J5: 0826-1G1T-23-F; BEL_0826-1G1T-23-F
R17, R18: 100; R_0603_1608Metric

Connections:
LED5_0: J5.13; also elsewhere on the board
LED5_1: J5.15; also elsewhere on the board
unnamed: J5.14, R17.2
unnamed: J5.16, R18.2
unnamed: C49.2, J5.12 (TRCT1)
unnamed: C50.2, J5.6 (TRCT2)
unnamed: C51.2, J5.1 (TRCT3)
unnamed: C48.2, J5.7 (TRCT4)
SGND: J5.S1 (SHIELD), J5.S2 (SHIELD__1); also elsewhere on the board
TXRX5_A+: J5.11 (TRD1+); also elsewhere on the board
TXRX5_A-: J5.10 (TRD1-); also elsewhere on the board
TXRX5_B+: J5.4 (TRD2+); also elsewhere on the board
TXRX5_B-: J5.5 (TRD2-); also elsewhere on the board
TXRX5_C+: J5.3 (TRD3+); also elsewhere on the board
TXRX5_C-: J5.2 (TRD3-); also elsewhere on the board
TXRX5_D+: J5.8 (TRD4+); also elsewhere on the board
TXRX5_D-: J5.9 (TRD4-); also elsewhere on the board

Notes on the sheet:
LEDx_1 pin indicates the link status LEDx_0 pin indicates the activity status
